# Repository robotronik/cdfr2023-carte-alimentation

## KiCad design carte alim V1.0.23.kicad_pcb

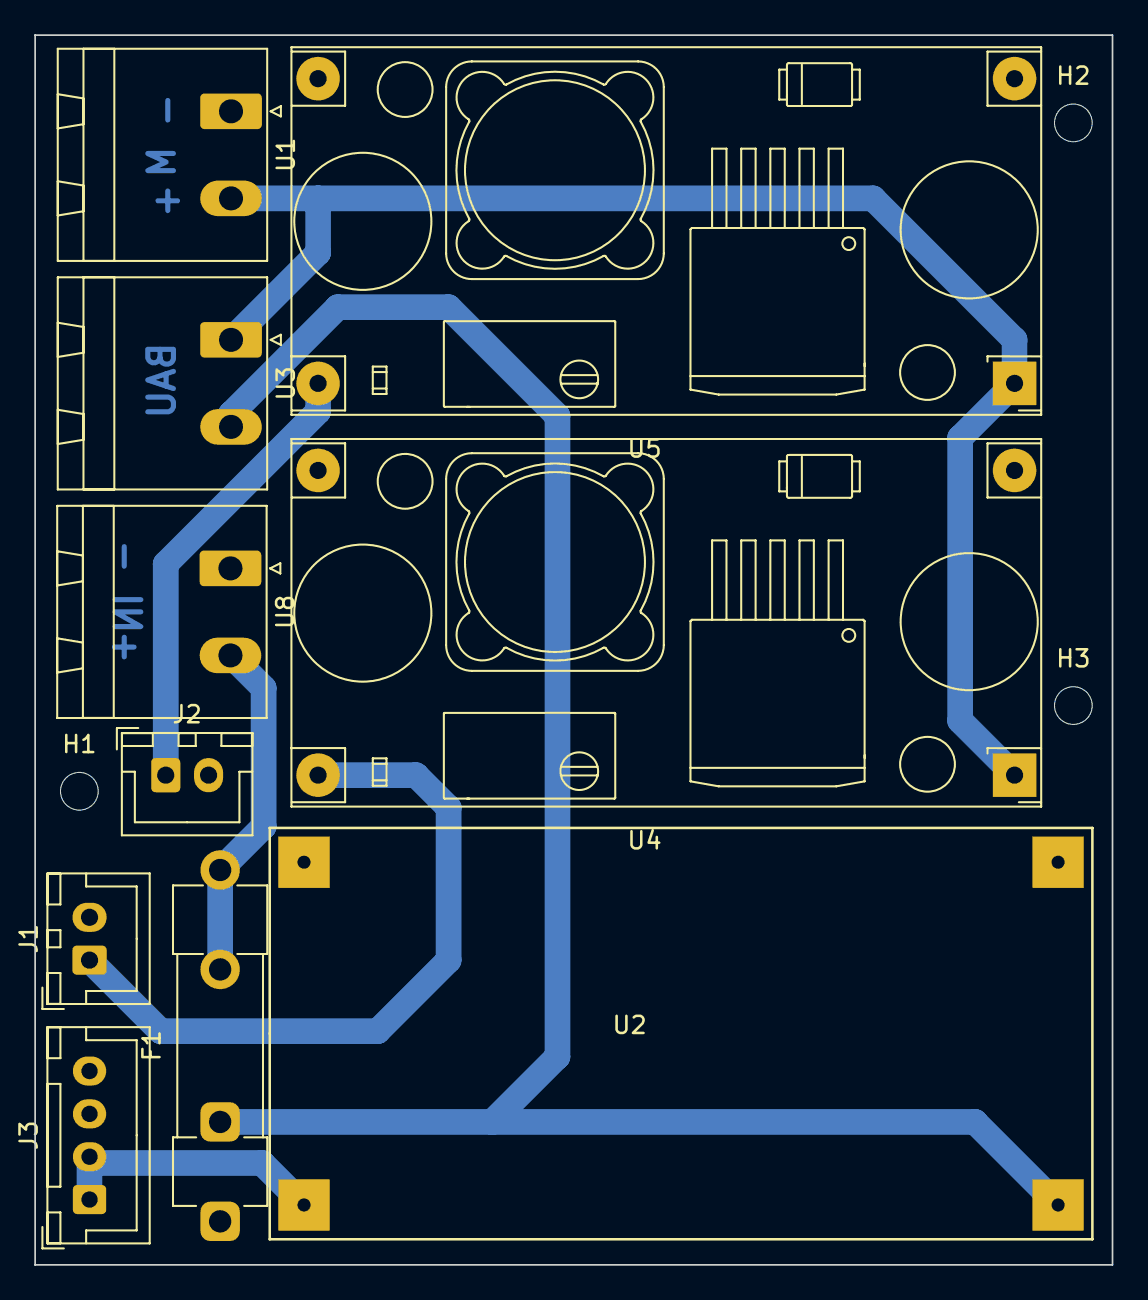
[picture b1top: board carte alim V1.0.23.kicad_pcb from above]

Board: 2 copper layers, 62.9 x 71.8 mm, 13 parts (0 on the bottom side), 7 nets.

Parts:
F1: Fuse; Fuseholder_Clip-5x20mm_Littelfuse_520_Inline_P20.50x5.80mm_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
H1, H2, H3: MountingHole; MountingHole_2.2mm_M2_ISO7380
J1, J2: Conn_01x02; JST_XH_B2B-XH-A_1x02_P2.50mm_Vertical
J3: Conn_01x04; JST_XH_B4B-XH-A_1x04_P2.50mm_Vertical
U1, U3, U8: B_Plug_5mm; PhoenixContact_MSTBA_2,5_2-G-5,08_1x02_P5.08mm_Horizontal
U2: XL4015; XL4015_Converter
U4, U5: YAAJ_DCDC_StepDown_LM2596

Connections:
14.4_VBattery: F1.2, U8.2
GND: J1.2, J2.2, J3.3, J3.4, U1.1, U2.2 (IN-), U2.4 (OUT-), U4.2 (GND), U4.3 (GND), U5.2 (GND), U5.3 (GND), U8.1
unnamed: J1.1, U4.4 (Vout)
unnamed: J2.1, U5.4 (Vout)
unnamed: J3.1, J3.2, U2.3 (OUT+)
unnamed: F1.1, U2.1 (IN+), U3.2
unnamed: U1.2, U3.1, U4.1 (Vin), U5.1 (Vin)

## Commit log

2023-05-09 new carte
2023-05-10 carte final V3
